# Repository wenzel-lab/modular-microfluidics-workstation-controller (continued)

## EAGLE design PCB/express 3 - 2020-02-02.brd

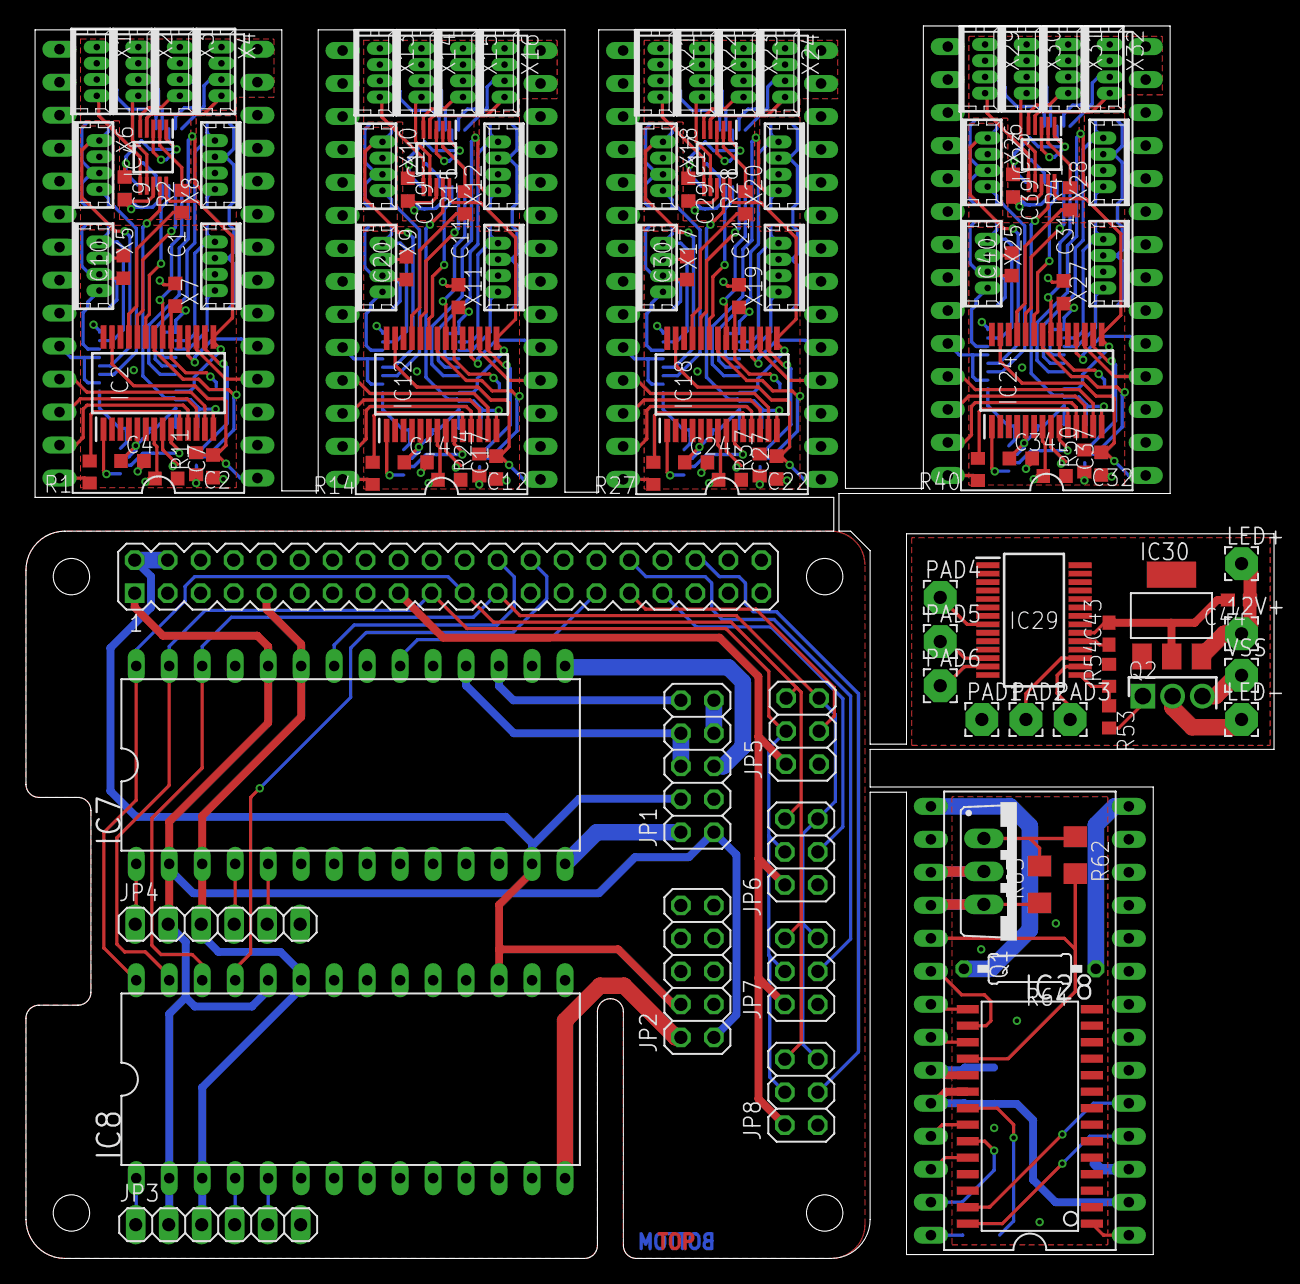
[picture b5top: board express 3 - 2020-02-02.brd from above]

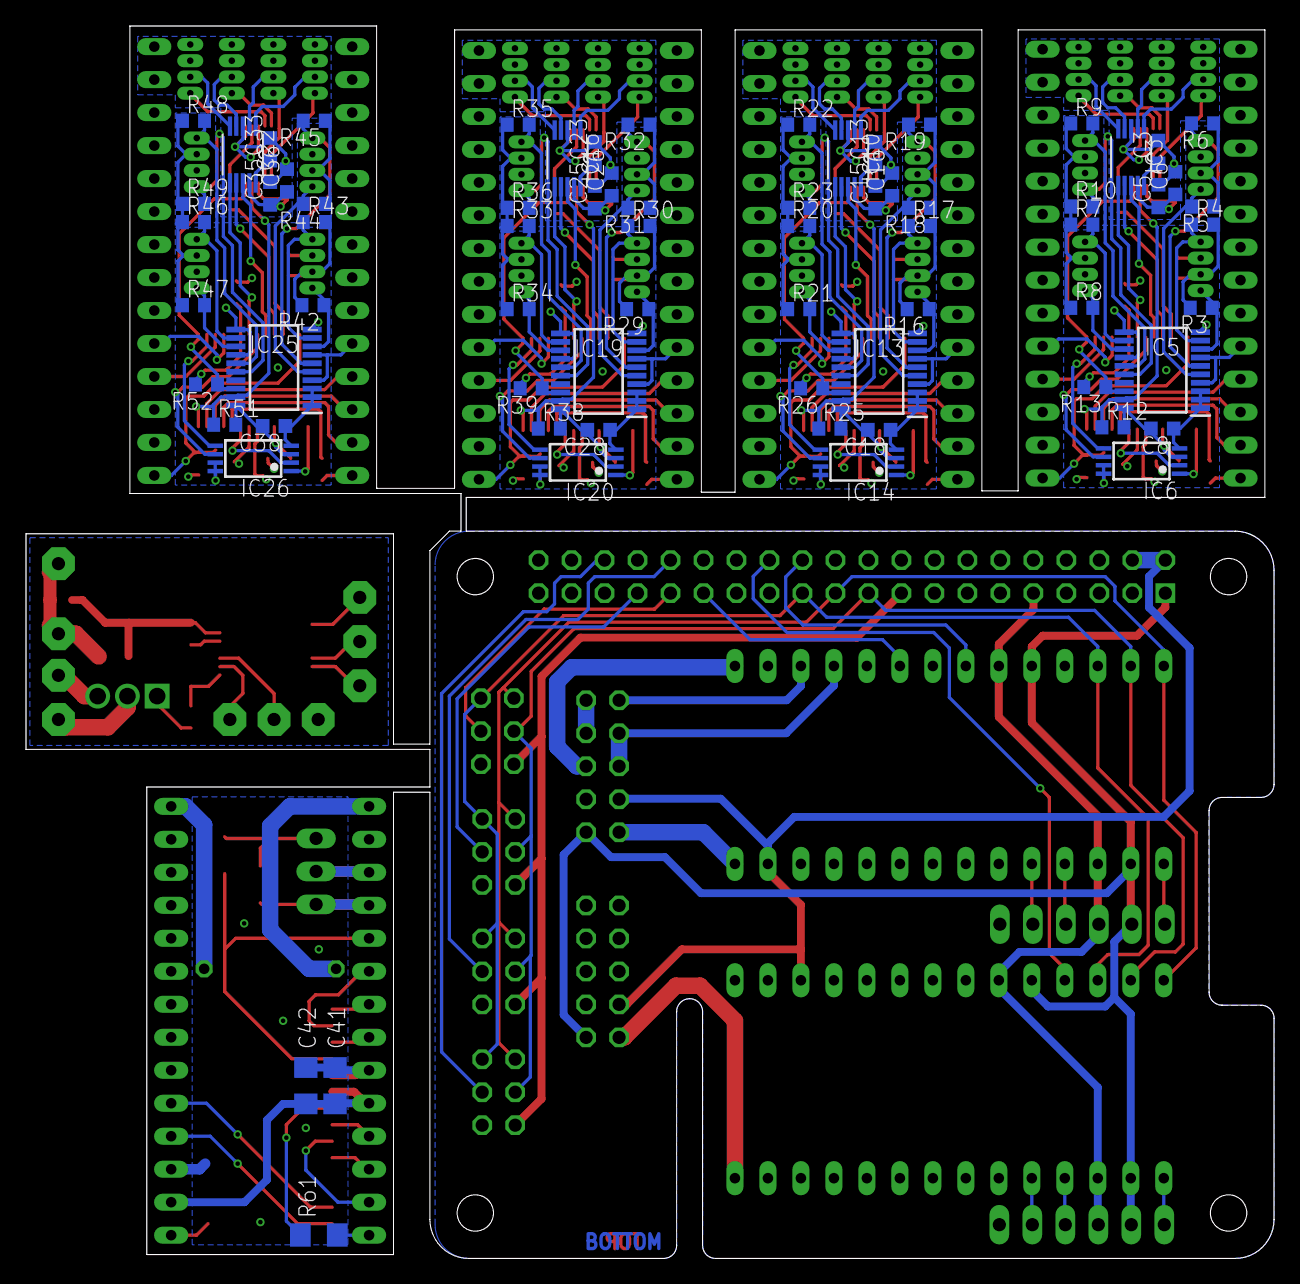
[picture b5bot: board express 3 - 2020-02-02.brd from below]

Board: 4 copper layers, 96.1 x 94.9 mm, 185 parts (71 on the bottom side), 213 nets.

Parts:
12V+: WIREPAD2,54/1,0; 2,54/1,0
C1, C2, C3, C4, C5, C6, C7, C8, C9, C10, C11, C12, C13, C14, C15, C16, C17, C18, C19, C20, C21, C22, C23, C24, C25, C26, C27, C28, C29, C30, C31, C32, C33, C34, C35, C36, C37, C38, C39, C40: C0603K
C41, C42: C1206
C43, C44: C0603
IC1, IC7, IC8, IC9, IC15, IC21, IC27: DIL28-6
IC2, IC12, IC18, IC24: DSPIC33CK256MP502-I_SS; SOP65P780X200-28N
IC3, IC10, IC16, IC22: AD5624R; SOP50P490X110-10N
IC4, IC11, IC17, IC23: ADS1115; SOP50P490X110-10N
IC5, IC13, IC19, IC25: PCA9544APW,112; SOP65P640X110-20N
IC6, IC14, IC20, IC26: 25AA040ST; TSSOP8
IC28: PIC16F18857; SO28W
IC29: PIC16F18857T-I_SS; SOP65P780X200-28N
IC30: REG1117; SOT223
JP1, JP2: 2X05
JP3, JP4: 1X06
JP5, JP6, JP7, JP8: 2X03
K1: PIN20X2; PIN_20X2
LED+: WIREPAD2,54/1,0; 2,54/1,0
LED-: WIREPAD2,54/1,0; 2,54/1,0
PAD1, PAD2, PAD3, PAD4, PAD5, PAD6: WIREPAD2,54/1,0; 2,54/1,0
Q1: TO220BV
Q2: AUIRFU8403; TO229P239X654X978-3P
R1, R2, R3, R4, R5, R6, R7, R8, R9, R10, R11, R12, R13, R14, R15, R16, R17, R18, R19, R20, R21, R22, R23, R24, R25, R26, R27, R28, R29, R30, R31, R32, R33, R34, R35, R36, R37, R38, R39, R40, R41, R42, R43, R44, R45, R46, R47, R48, R49, R50, R51, R52, R53, R54: R0603
R61, R62, R63: R1206
R64: 0207/10
VSS: WIREPAD2,54/1,0; 2,54/1,0
X1, X2, X3, X4, X5, X6, X7, X8, X9, X10, X11, X12, X13, X14, X15, X16, X17, X18, X19, X20, X21, X22, X23, X24, X25, X26, X27, X28, X29, X30, X31, X32: 53047-04

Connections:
0V: IC7.18, JP1.6, JP1.8
+3V1: IC7.2, IC7.24, IC8.2, IC8.24, JP1.1, JP2.1, JP3.2, JP4.2, JP5.2, JP6.2, JP7.2, JP8.2, K1.1, K1.17
+3V2: C11.1, C12.1, C14.1, C18.2, C20.1, IC9.2, IC9.24, IC12.5, IC12.7, IC12.20, IC13.4, IC13.7, IC13.11, IC13.14, IC13.20, IC14.3, IC14.7, IC14.8, R16.2, R17.2, R18.1, R19.1, R20.1, R21.1, R22.1, R23.1, R24.1, R25.2, R26.2, X9.2, X10.2, X11.2, X12.2
+3V3: C1.1, C2.1, C4.1, C8.2, C10.1, IC1.2, IC1.24, IC2.5, IC2.7, IC2.20, IC5.4, IC5.7, IC5.11, IC5.14, IC5.20, IC6.3, IC6.7, IC6.8, R3.2, R4.2, R5.1, R6.1, R7.1, R8.1, R9.1, R10.1, R11.1, R12.2, R13.2, X5.2, X6.2, X7.2, X8.2
+3V4: C21.1, C22.1, C24.1, C28.2, C30.1, IC15.2, IC15.24, IC18.5, IC18.7, IC18.20, IC19.4, IC19.7, IC19.11, IC19.14, IC19.20, IC20.3, IC20.7, IC20.8, R29.2, R30.2, R31.1, R32.1, R33.1, R34.1, R35.1, R36.1, R37.1, R38.2, R39.2, X17.2, X18.2, X19.2, X20.2
+3V5: C31.1, C32.1, C34.1, C38.2, C40.1, IC21.2, IC21.24, IC24.5, IC24.7, IC24.20, IC25.4, IC25.7, IC25.11, IC25.14, IC25.20, IC26.3, IC26.7, IC26.8, R42.2, R43.2, R44.1, R45.1, R46.1, R47.1, R48.1, R49.1, R50.1, R51.2, R52.2, X25.2, X26.2, X27.2, X28.2
+5V: C5.1, C6.1, C9.2, IC1.17, IC3.9, IC4.8
+5V1: IC7.13, IC8.17, JP1.4, JP2.4, K1.2, K1.4
+5V2: C15.1, C16.1, C19.2, IC9.17, IC10.9, IC11.8
+5V3: C25.1, C26.1, C29.2, IC15.17, IC16.9, IC17.8
+5V4: C35.1, C36.1, C39.2, IC21.17, IC22.9, IC23.8
+5V6: C43.2, C44.2, IC29.20, IC30.2
+12V: IC1.14, X1.4, X2.4, X3.4, X4.4
+12V1: IC7.14, IC8.14, JP1.2, JP2.2
+12V2: IC9.14, X13.4, X14.4, X15.4, X16.4
+12V3: IC15.14, X21.4, X22.4, X23.4, X24.4
+12V4: IC21.14, X29.4, X30.4, X31.4, X32.4
+12V5: IC27.14, R64.1
+12V6: 12V+.1, C44.1, IC30.3, LED+.1
ADC_RDY: IC2.25, R2.1
ADC_RDY1: IC12.25, R15.1
ADC_RDY2: IC18.25, R28.1
ADC_RDY3: IC24.25, R41.1
CE0: IC7.22, K1.24
CE1: IC8.25, K1.26
GND: C1.2, C2.2, C3.2, C4.2, C5.2, C6.2, C7.1, C8.1, C9.1, C10.2, IC1.3, IC1.13, IC1.23, IC2.6, IC2.8, IC2.19, IC3.3, IC4.1, IC4.3, IC5.1, IC5.2, IC5.3, IC5.10, IC6.4, X1.3, X2.3, X3.3, X4.3, X5.3, X6.3, X7.3, X8.3
GND1: IC7.3, IC7.23, IC8.3, IC8.13, IC8.23, JP1.3, JP2.3, JP3.3, JP4.3, JP5.1, JP6.1, JP7.1, JP8.1, K1.6, K1.9, K1.14, K1.20, K1.25, K1.30, K1.34, K1.39
GND2: C11.2, C12.2, C13.2, C14.2, C15.2, C16.2, C17.1, C18.1, C19.1, C20.2, IC9.3, IC9.13, IC9.23, IC10.3, IC11.1, IC11.3, IC12.6, IC12.8, IC12.19, IC13.1, IC13.2, IC13.3, IC13.10, IC14.4, X9.3, X10.3, X11.3, X12.3, X13.3, X14.3, X15.3, X16.3
GND3: C21.2, C22.2, C23.2, C24.2, C25.2, C26.2, C27.1, C28.1, C29.1, C30.2, IC15.3, IC15.13, IC15.23, IC16.3, IC17.1, IC17.3, IC18.6, IC18.8, IC18.19, IC19.1, IC19.2, IC19.3, IC19.10, IC20.4, X17.3, X18.3, X19.3, X20.3, X21.3, X22.3, X23.3, X24.3
GND4: C31.2, C32.2, C33.2, C34.2, C35.2, C36.2, C37.1, C38.1, C39.1, C40.2, IC21.3, IC21.13, IC21.23, IC22.3, IC23.1, IC23.3, IC24.6, IC24.8, IC24.19, IC25.1, IC25.2, IC25.3, IC25.10, IC26.4, X25.3, X26.3, X27.3, X28.3, X29.3, X30.3, X31.3, X32.3
GND5: C41.2, C42.2, IC27.3, IC27.23, IC28.8, IC28.19
GPIO6: JP5.3, K1.31
GPIO12: JP7.3, K1.32
GPIO13: JP6.3, K1.33
GPIO16: JP8.3, K1.36
I2C_SCL: IC2.15, IC4.10, IC5.18, R13.1
I2C_SCL1: IC11.10, IC12.15, IC13.18, R26.1
I2C_SCL2: IC17.10, IC18.15, IC19.18, R39.1
I2C_SCL3: IC23.10, IC24.15, IC25.18, R52.1
I2C_SDA: IC2.14, IC4.9, IC5.19, R12.1
I2C_SDA1: IC11.9, IC12.14, IC13.19, R25.1
I2C_SDA2: IC17.9, IC18.14, IC19.19, R38.1
I2C_SDA3: IC23.9, IC24.14, IC25.19, R51.1
ICSP_MCLR: C7.2, IC1.1, IC2.27, R11.2
ICSP_MCLR1: IC8.1, JP3.1
ICSP_MCLR2: IC7.1, JP4.1
ICSP_MCLR3: C17.2, IC9.1, IC12.27, R24.2
ICSP_MCLR4: C27.2, IC15.1, IC18.27, R37.2
ICSP_MCLR5: C37.2, IC21.1, IC24.27, R50.2
ICSP_MCLR6: IC27.1, IC28.1
ICSP_PGC: IC1.5, IC2.18
ICSP_PGC1: IC8.5, JP3.5
ICSP_PGC2: IC7.5, JP4.5
ICSP_PGC3: IC9.5, IC12.18
ICSP_PGC4: IC15.5, IC18.18
ICSP_PGC5: IC21.5, IC24.18
ICSP_PGD: IC1.4, IC2.17
ICSP_PGD1: IC8.4, JP3.4
ICSP_PGD2: IC7.4, JP4.4
ICSP_PGD3: IC9.4, IC12.17
ICSP_PGD4: IC15.4, IC18.17
ICSP_PGD5: IC21.4, IC24.17
ICSP_PGD6: IC27.4, IC28.28
LED_-: LED-.1, Q2.2
LED_LOW: IC29.15, R53.1, R54.1
MISO: IC7.28, IC8.28, JP5.6, JP6.6, JP7.6, JP8.6, K1.21
MOSI: IC7.27, IC8.27, JP5.4, JP6.4, JP7.4, JP8.4, K1.19
unnamed: C3.1, IC3.10
unnamed: IC3.1, X1.2
unnamed: IC11.2, R15.2
unnamed: IC11.5, X15.1
unnamed: C13.1, IC10.10
unnamed: IC3.2, X2.2
unnamed: IC3.4, X3.2
unnamed: IC4.2, R2.2
unnamed: IC10.1, X13.2
unnamed: IC4.5, X3.1
unnamed: IC3.5, X4.2
unnamed: IC5.5, R5.2, X6.1
unnamed: IC5.6, R6.2, X6.4
unnamed: IC5.8, R3.1, X5.1
unnamed: IC5.9, R4.1, X5.4
unnamed: IC5.12, R7.2, X7.1
unnamed: IC5.13, R8.2, X7.4
unnamed: IC5.15, R9.2, X8.1
unnamed: IC5.16, R10.2, X8.4
unnamed: IC4.7, X2.1
unnamed: IC10.2, X14.2
unnamed: IC4.6, X1.1
unnamed: IC4.4, X4.1
unnamed: IC10.4, X15.2
unnamed: IC10.5, X16.2
unnamed: IC13.12, R20.2, X11.1
unnamed: IC13.13, R21.2, X11.4
unnamed: IC13.15, R22.2, X12.1
unnamed: IC13.16, R23.2, X12.4
unnamed: IC13.5, R18.2, X10.1
unnamed: IC13.6, R19.2, X10.4
unnamed: IC13.8, R16.1, X9.1
unnamed: IC13.9, R17.1, X9.4
unnamed: IC11.7, X14.1
unnamed: IC11.6, X13.1
unnamed: IC11.4, X16.1
unnamed: IC17.2, R28.2
unnamed: IC17.5, X23.1
unnamed: C23.1, IC16.10
unnamed: IC16.1, X21.2
unnamed: IC16.2, X22.2
unnamed: IC16.4, X23.2
unnamed: IC16.5, X24.2
unnamed: IC19.12, R33.2, X19.1
unnamed: IC19.13, R34.2, X19.4
unnamed: IC19.15, R35.2, X20.1
unnamed: IC19.16, R36.2, X20.4
unnamed: IC19.5, R31.2, X18.1
unnamed: IC19.6, R32.2, X18.4
unnamed: IC19.8, R29.1, X17.1
unnamed: IC19.9, R30.1, X17.4
unnamed: IC17.7, X22.1
unnamed: IC17.6, X21.1
unnamed: IC17.4, X24.1
unnamed: IC23.2, R41.2
unnamed: IC23.5, X31.1
unnamed: C33.1, IC22.10
unnamed: IC22.1, X29.2
unnamed: IC22.2, X30.2
unnamed: IC22.4, X31.2
unnamed: IC22.5, X32.2
unnamed: IC25.12, R46.2, X27.1
unnamed: IC25.13, R47.2, X27.4
unnamed: IC25.15, R48.2, X28.1
unnamed: IC25.16, R49.2, X28.4
unnamed: IC25.5, R44.2, X26.1
unnamed: IC25.6, R45.2, X26.4
unnamed: IC25.8, R42.1, X25.1
unnamed: IC25.9, R43.1, X25.4
unnamed: IC23.7, X30.1
unnamed: IC23.6, X29.1
unnamed: IC23.4, X32.1
unnamed: IC27.25, IC28.22
unnamed: IC28.21, R61.2
unnamed: IC27.5, IC28.27
unnamed: Q1.G, R62.1, R63.2
unnamed: IC27.21, IC28.15
unnamed: Q2.1, R53.2
SCLK: IC7.26, IC8.26, JP5.5, JP6.5, JP7.5, JP8.5, K1.23
SPI2_DAC_CLK: IC2.24, IC3.7
SPI2_DAC_CLK1: IC10.7, IC12.24
SPI2_DAC_CLK2: IC16.7, IC18.24
SPI2_DAC_CLK3: IC22.7, IC24.24
SPI2_DAC_MOSI: IC2.23, IC3.8
SPI2_DAC_MOSI1: IC10.8, IC12.23
SPI2_DAC_MOSI2: IC16.8, IC18.23
SPI2_DAC_MOSI3: IC22.8, IC24.23
SPI2_DAC_SYNC: IC2.21, IC3.6
SPI2_DAC_SYNC1: IC10.6, IC12.21
SPI2_DAC_SYNC2: IC16.6, IC18.21
SPI2_DAC_SYNC3: IC22.6, IC24.21
SPI3_EE_CLK: IC2.22, IC6.6
SPI3_EE_CLK1: IC12.22, IC14.6
SPI3_EE_CLK2: IC18.22, IC20.6
SPI3_EE_CLK3: IC24.22, IC26.6
SPI3_EE_MISO: IC2.9, IC6.2
SPI3_EE_MISO1: IC12.9, IC14.2
SPI3_EE_MISO2: IC18.9, IC20.2
SPI3_EE_MISO3: IC24.9, IC26.2
SPI3_EE_MOSI: IC2.16, IC6.5
SPI3_EE_MOSI1: IC12.16, IC14.5
SPI3_EE_MOSI2: IC18.16, IC20.5
SPI3_EE_MOSI3: IC24.16, IC26.5
SPI3_EE_SS: IC2.1, IC6.1
SPI3_EE_SS1: IC12.1, IC14.1
SPI3_EE_SS2: IC18.1, IC20.1
SPI3_EE_SS3: IC24.1, IC26.1
SPI_CLK: IC1.26, IC2.12
SPI_CLK1: IC9.26, IC12.12
SPI_CLK2: IC15.26, IC18.12
SPI_CLK3: IC21.26, IC24.12
SPI_CLK4: IC27.26, IC28.24
SPI_IN: IC1.27, IC2.11
SPI_IN1: IC9.27, IC12.11
SPI_IN2: IC15.27, IC18.11
SPI_IN3: IC21.27, IC24.11
SPI_IN4: IC27.27, IC28.23
SPI_OUT: IC1.28, R1.2
SPI_OUT1: IC9.28, R14.2
SPI_OUT2: IC15.28, R27.2
SPI_OUT3: IC21.28, R40.2
SPI_OUT4: IC27.28, R61.1
SPI_OUT_R: IC2.10, R1.1
SPI_OUT_R1: IC12.10, R14.1
SPI_OUT_R2: IC18.10, R27.1
SPI_OUT_R3: IC24.10, R40.1
SPI_SS: IC1.25, IC2.13
SPI_SS1: IC9.25, IC12.13
SPI_SS2: IC15.25, IC18.13
SPI_SS3: IC21.25, IC24.13
SPI_SS4: IC27.22, IC28.17
STROBE+: JP1.7, JP1.9
STROBE+_RES: IC7.15, JP1.5
STROBE+_RES1: IC27.15, R64.2
STROBE-: IC7.17, JP1.10
STROBE-1: IC27.17, Q1.D
STROBE_0V: IC27.18, Q1.S, R63.1
STROBE_GATE1: IC27.19, IC28.18, R62.2
STROBE_TRIG_IN: IC7.20, K1.29
STROBE_TRIG_IN1: IC27.20, IC28.16
SW1.1: IC29.17, PAD2.1
SW1.2: IC29.16, PAD3.1
SW2.1: IC29.12, PAD5.1
SW2.2: IC29.13, PAD6.1
V+: C41.1, C42.1, IC27.2, IC27.24, IC28.20
VSS: C43.1, IC29.8, IC29.19, IC30.1, PAD1.1, PAD4.1, Q2.3, R54.2, VSS.1

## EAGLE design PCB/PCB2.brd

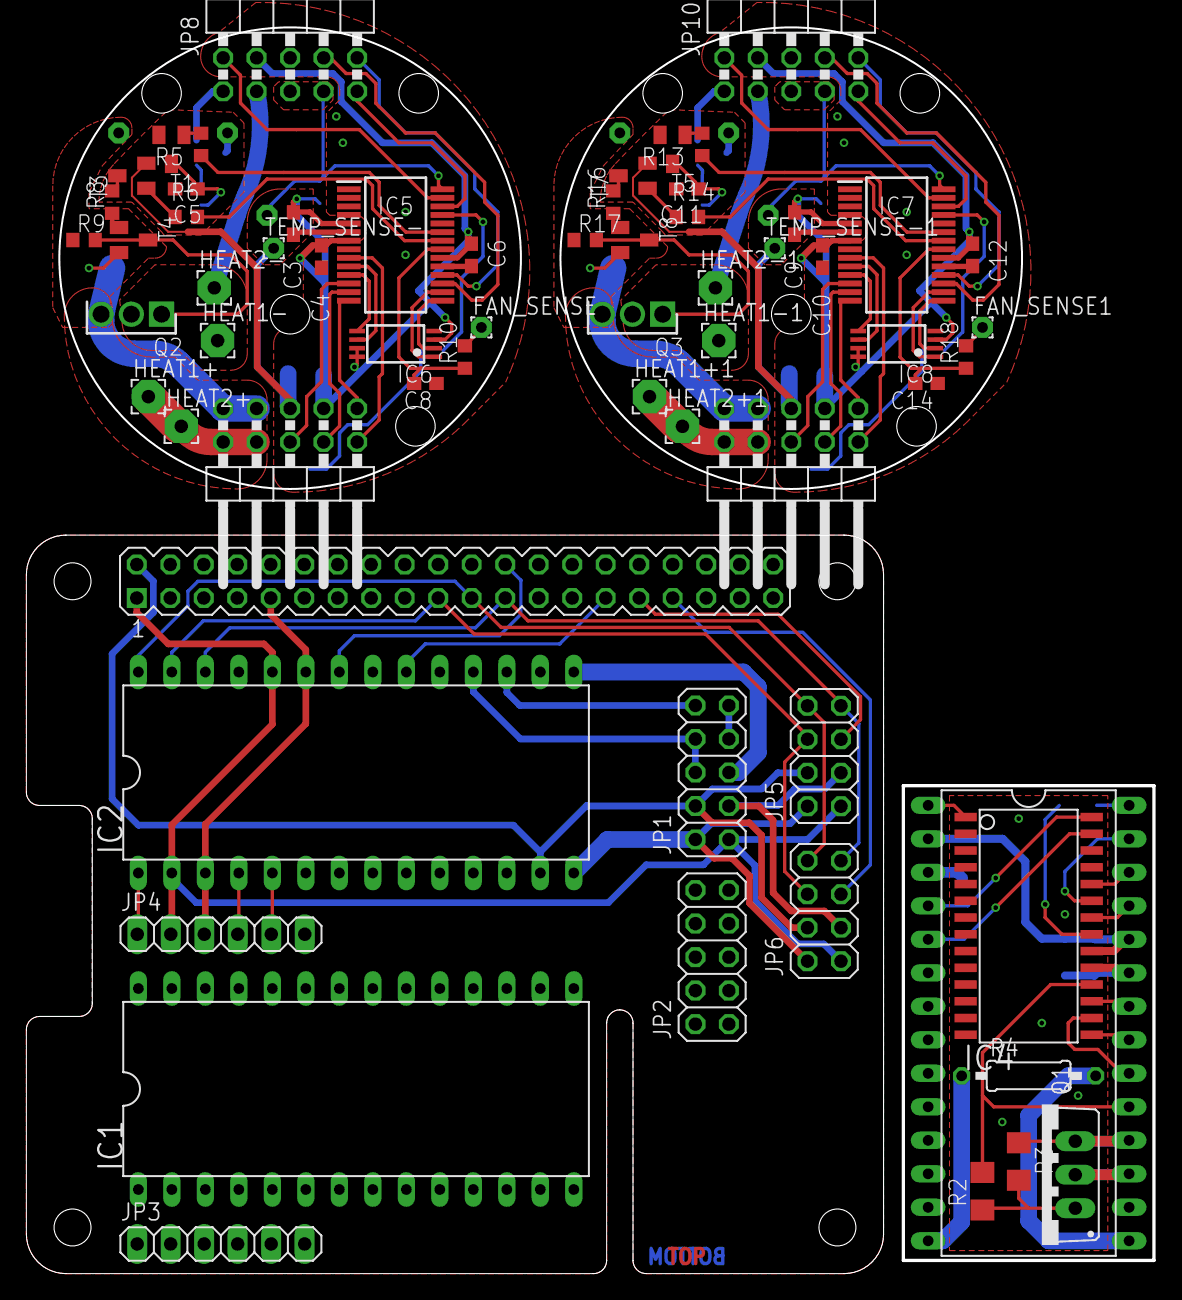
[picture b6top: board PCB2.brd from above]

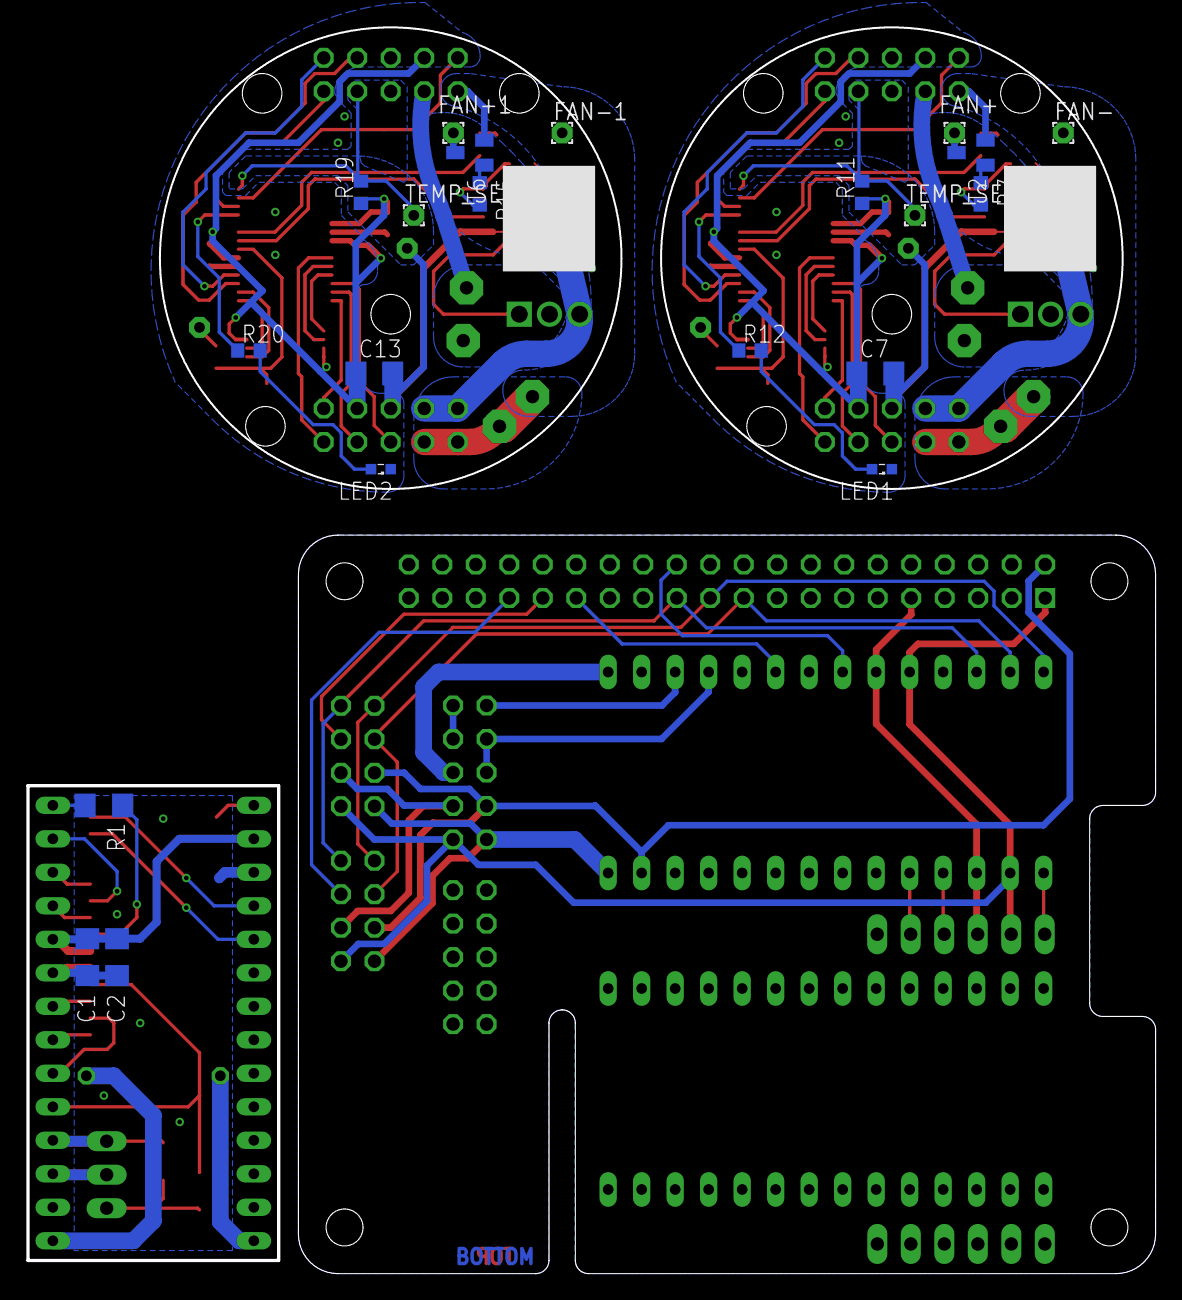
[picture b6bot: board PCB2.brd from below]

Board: 2 copper layers, 85.5 x 94.5 mm, 84 parts (21 on the bottom side), 101 nets.

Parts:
C1, C2, C7, C13: C1206
C3, C4, C5, C6, C8, C9, C10, C11, C12, C14: C0603
FAN+, FAN+1: 1,6/0,8
FAN-, FAN-1: 1,6/0,8
FAN_SENSE, FAN_SENSE1: 1,6/0,8
HEAT1+, HEAT1+1, HEAT1-, HEAT1-1, HEAT2+, HEAT2+1, HEAT2-, HEAT2-1: 2,54/1,0
IC1, IC2, IC3: DIL28-6
IC4: PIC16F18857; SO28W
IC5, IC7: DSPIC33CK256MP502-I_SS; SOP65P780X200-28N
IC6, IC8: 25AA040ST; TSSOP8
JP1, JP2: 2X05
JP3, JP4: 1X06
JP5, JP6: 2X04
JP7, JP8, JP9, JP10: 2X05/90
K1: PIN20X2; PIN_20X2
LED1, LED2: SML0603
Q1: TO220BV
Q2, Q3: AUIRFU8403; TO229P239X654X978-3P
R1, R2, R3: R1206
R4: 0207/10
R5, R6, R7, R8, R9, R10, R11, R12, R13, R14, R15, R16, R17, R18, R19, R20: R0603
T1, T2, T3, T4, T5, T6, T7, T8: SOT23-BEC
TEMP_SENSE+, TEMP_SENSE+1: 1,6/0,8
TEMP_SENSE-, TEMP_SENSE-1: 1,6/0,8

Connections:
0V: IC2.18, JP1.6, JP1.8
0V1: FAN-.1, JP7.7, JP7.9, Q2.3, R9.1
0V2: FAN-1.1, JP9.7, JP9.9, Q3.3, R17.1
+3V1: C3.1, C4.1, C6.1, C7.1, IC5.5, IC5.7, IC5.20, IC6.3, IC6.7, IC6.8, JP7.3, JP8.4, R11.1
+3V2: C9.1, C10.1, C12.1, C13.1, IC7.5, IC7.7, IC7.20, IC8.3, IC8.7, IC8.8, JP9.3, JP10.4, R19.1
+3V3: IC2.2, IC2.24, JP1.1, JP4.2, JP5.1, JP6.1, K1.1, K1.17
+5V: IC2.13, JP1.4, JP5.4, JP6.4, K1.2, K1.4
+12V: IC2.14, JP1.2, JP5.2, JP6.2
+12V1: IC3.14, R4.1
+12V2: HEAT1+.1, HEAT2+.1, JP7.8, JP7.10, JP8.1, T2.E, T4.E
+12V3: HEAT1+1.1, HEAT2+1.1, JP9.8, JP9.10, JP10.1, T6.E, T8.E
CE0: IC2.22, K1.24
FAN+: FAN+.1, T2.C
FAN+1: FAN+1.1, T6.C
FAN_SENSE: C8.2, IC5.21, R10.1
FAN_SENSE1: C14.2, IC7.21, R18.1
GND: IC2.3, IC2.23, JP1.3, JP4.3, JP5.3, JP6.3, K1.6, K1.9, K1.14, K1.20, K1.25, K1.30, K1.34, K1.39
GND1: C1.2, C2.2, IC3.3, IC3.23, IC4.8, IC4.19
GND2: C3.2, C4.2, C5.2, C6.2, C7.2, C8.1, IC5.6, IC5.8, IC5.19, IC6.4, JP7.5, JP8.5, JP8.6, LED1.C, T1.E, T3.E, TEMP_SENSE-.1
GND3: C9.2, C10.2, C11.2, C12.2, C13.2, C14.1, IC7.6, IC7.8, IC7.19, IC8.4, JP9.5, JP10.5, JP10.6, LED2.C, T5.E, T7.E, TEMP_SENSE-1.1
GPIO6: JP5.5, K1.31
GPIO13: JP6.5, K1.33
HEAT-: HEAT1-.1, HEAT2-.1, JP8.3, Q2.2
HEAT-1: HEAT1-1.1, HEAT2-1.1, JP10.3, Q3.2
ICSP_MCLR: IC2.1, JP4.1
ICSP_PGC: IC2.5, JP4.5
ICSP_PGD: IC2.4, JP4.4
ISCP_PGD: IC3.4, IC4.28
MCLR: IC5.27, JP8.2
MCLR1: IC7.27, JP10.2
MISO: IC2.28, JP5.8, JP6.8, K1.21
MOSI: IC2.27, JP5.6, JP6.6, K1.19
unnamed: IC3.25, IC4.22
unnamed: IC4.21, R1.2
unnamed: R8.2, T3.C
unnamed: R8.1, T4.B
unnamed: IC3.5, IC4.27
unnamed: R5.1, T1.B
unnamed: C5.1, R7.2, T1.C
unnamed: R7.1, T2.B
unnamed: Q1.G, R2.1, R3.2
unnamed: R6.1, T3.B
unnamed: IC3.21, IC4.15
unnamed: Q2.1, R9.2, T4.C
unnamed: FAN_SENSE.1, R10.2
unnamed: IC5.11, IC6.5
unnamed: IC5.10, IC6.6
unnamed: IC5.15, IC6.2
unnamed: IC5.16, IC6.1
unnamed: IC5.22, R6.2
unnamed: IC5.23, R5.2
unnamed: LED1.A, R12.2
unnamed: IC5.25, R12.1
unnamed: R13.1, T5.B
unnamed: R15.1, T6.B
unnamed: C11.1, R15.2, T5.C
unnamed: R16.2, T7.C
unnamed: R16.1, T8.B
unnamed: R14.1, T7.B
unnamed: Q3.1, R17.2, T8.C
unnamed: FAN_SENSE1.1, R18.2
unnamed: IC7.11, IC8.5
unnamed: IC7.10, IC8.6
unnamed: IC7.15, IC8.2
unnamed: IC7.16, IC8.1
unnamed: IC7.22, R14.2
unnamed: IC7.23, R13.2
unnamed: LED2.A, R20.2
unnamed: IC7.25, R20.1
PGC: IC5.18, JP8.10
PGC1: IC7.18, JP10.10
PGD: IC5.17, JP8.8
PGD1: IC7.17, JP10.8
SCLK: IC2.26, JP5.7, JP6.7, K1.23
SPI1: IC5.9, JP7.2
SPI2: IC5.12, JP7.6
SPI3: IC5.13, JP7.4
SPI4: IC5.14, JP7.1
SPI5: IC7.9, JP9.2
SPI6: IC7.12, JP9.6
SPI7: IC7.13, JP9.4
SPI8: IC7.14, JP9.1
SPI_CLOCK: IC3.26, IC4.24
SPI_IN: IC3.27, IC4.23
SPI_MCLR: IC3.1, IC4.1
SPI_OUT: IC3.28, R1.1
SPI_SS: IC3.22, IC4.17
STROBE+: JP1.7, JP1.9
STROBE+_RES: IC2.15, JP1.5
STROBE+_RES1: IC3.15, R4.2
STROBE-: IC2.17, JP1.10
STROBE-1: IC3.17, Q1.D
STROBE_0V: IC3.18, Q1.S, R3.1
STROBE_GATE1: IC3.19, IC4.18, R2.2
STROBE_TRIG_IN: IC2.20, K1.29
STROBE_TRIG_IN1: IC3.20, IC4.16
TEMP_SENSE: IC5.28, JP8.7, R11.2, TEMP_SENSE+.1
TEMP_SENSE1: IC7.28, JP10.7, R19.2, TEMP_SENSE+1.1
TX: IC5.26, JP8.9
TX1: IC7.26, JP10.9
V+: C1.1, C2.1, IC3.2, IC3.24, IC4.20

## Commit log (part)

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2019-08-20 Create blank
2019-10-01 nbproject folder added.
2019-10-01 All files added. Can output 2ms pulse after camera start pulse.
2019-10-03 Can set strobe timing via time parameters.
2019-10-04 Adding CLC code.
2019-10-04 SPI strobe interface working.
2019-10-05 STX added.
2019-10-05 Checksum and corruption test.
2019-10-05 Created basic packet routines.
2019-10-07 Fixed MAX_TIME_NS and strobe timing packet parse.
2019-10-08 Strobe MAX_TIME_NS fixed.
2019-10-08 Fixed abs calculation in find_scalers_time. Changed TMR2 to trigger on transition instead of level - this allows strobe optionally to be on during closing shutter. Had to leave TMR4 on to make this w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
2019-10-08 Added strobe camera class. Attempts to calculate camera timing.
2019-10-08 New time calculations.
2019-10-11 Testing GUI development.
2019-10-12 Strobe PIC return comms.
2019-10-14 Auto adjust camera timing using camera read back time capture.
2019-10-19 Initial PCB for strobe module.
2019-10-19 Raspberry Pi 4 config to output camera "strobe" on GPIO.
2019-10-26 Initial commit. DAC write works.
2019-10-28 Continuous ADC conversion success.
2019-10-28 SPI test code compiles.
2019-10-29 SPI receive packets.
2019-10-30 SPI transmit modified not to write TX when not data to write (unlike with PIC16 series). Tests good.
2019-11-09 Started ADC <-> mbar conversion code. Starting ADS1115 implementation.
2019-11-10 ADS1115 working (polling).
2019-11-12 Fixed PIC clock. Added 1ms timer. I2C fixed - SEN was set while PEN - prevent manual ISR if PEN.
2019-11-14 Combined and improved ADS1115 I2C.
2019-11-15 ADC I2C polled for completion instead of waiting.
2019-11-19 Heater PID and simulated heater.
2019-11-20 Good temperature readings via UART. Heater heating manual power.
2019-12-05 Developing protocols and autotune status.
2019-12-05 Protocol working (ID and get temp). Changed IRQ priority such that SPI can't be interrupted.
2019-12-25 EEPROM and storage libraries created. Fan/stirrer output, speed measurement and control implemented.
2020-01-05 First strobe PCB submitted.
2020-01-05 Stirrer fan PID implemented. ADC trigger changed to timer. Measures 2.5us per sample x 16 = 40us filter interrupt.
2020-01-05 Submitting old PCB design before replacing with new design.
2020-01-05 First combined PCB for manufacture - pi hat, strobe, sample holder.
2020-01-16 Added resistor.
2020-01-16 Some config change?
2020-01-16 Stir interface + EEPROM added. LED added. Pins moved to match PCB. Fixed intermittent 10-bit readings - caused by reading filter register in main loop resetting RDY flag. 16-bit temperature readings.
2020-01-16 Minor changes to PCB: 1mm larger, MCLR resistor + cap added, thicker trace to external heater. Second manufacturing, not express.
2020-01-19 Added bulk cap and changed caps to Kemet, which have smaller keepout.
2020-01-19 Express manufacture - 4 layer pressure/flow board, pi hat, strobe.
2020-01-20 PCB modifications to get I2C on correct pins and use extra SPI for EEPROM. Code updated to match new pinout.
2020-01-21 ADC functional. Also fixed ADC RDY thresholds, which are 16-bit, not 8-bit.
2020-01-22 EEPROM working. DAC internal reference working.
2020-01-22 Storage added.
2020-01-26 Updated to match PCB. Programmed successfully, plugged into Pi Hat on Pi.
2020-01-28 Strobe PCB SPI working.
2020-01-28 Added PCA9544A I2C MUX and tested via Sensirion.
2020-01-29 Sensirion read flow/temp/flags implemented.
2020-01-30 Continuous pressure readings and pressure output, correctly scaled.
2020-02-01 More allowance between ICs and caps.
2020-02-02 Express PCB 3 ready.
2020-02-11 Caps moved to allow larger gaps near ADC, DAC, connector.
2020-02-11 Module headers replaced.
2020-02-11 Production commit.
2020-02-12 External strobe trigger added. Text and boxes added.
2020-02-16 Working on picommon.py, which controls SPI across all devices.
2020-02-16 Start of GUI.
2020-02-17 Added power limit setting. Expanded error capabilities.
2020-02-17 Heater display created as class. Fixed various general errors.
2020-02-23 New strobe interface code and GUI.
2020-02-23 Using piholderbox.py.
2020-02-23 Using pistrobebox.py.
2020-02-23 EEPROM storage save is now readwrite.
2020-02-23 Fan tuning. Save temps in EEPROM when set. Option to autotune for no overshoot. Saves power limit. Optional code to write current limit on start.
2020-02-24 Removed pull-ups on SDI and CLK. Problem caused by soldering and pull-ups were probably fine.
2020-02-25 Shipping.
2020-03-01 Changed fan sense resistor from 1k to 510, because at low speed the fan feedback would not pull low enough.
2020-03-01 Added SPI names.
2020-03-01 Added stir functions.
2020-03-06 Sample holder PCB images.
2020-03-06 Component placement images.
2020-03-07 Sample Holder image.
2020-03-10 EEPROM SS moved to RA1, tests OK. Snap programmer. Starting LG16 interface.
2020-03-10 Sensirion LG16 library working. Still need to integrate new functions.
2020-03-11 Restored lost changes. LG16 sensor now active, startup init added. Channel mapping added.
2020-03-13 Component values added.
2020-03-17 add more files for sample reservoirs
2020-03-19 image of 100ml reservoir added
2020-03-19 add bottle reservoir image
2020-03-19 remove unneeded old text
2020-03-23 Sample holder 3D images.
2020-03-25 ADC error handling. Pressure and flow control modes. Added control commands. LG16 flow sensor support.
2020-05-04 Creating Flask webapp.
2020-05-04 Automatic updates test.
2020-05-05 Continuous threaded updates working.
2020-05-08 Web interface for heater/piholder.
2020-05-09 Workaround for time.sleep in piholder.py and strobe.py. time.sleep would not return if the other thread blocked to obtain lock.
2020-05-09 Corrected initial copying of jinja strobe data. Added strobe period field using input box.
2020-05-10 Heater temperature set.
2020-05-11 Heater web interface complete.
2020-05-22 Mako camera test working.
2020-05-24 Camera html moved to separate file. Camera snapshot working. Camera thread is terminated on exit.
2020-05-29 Improvement of cap holder design
    Added fillets, so that the inner hexagon corners of the cap holder can be machined. 2mm rounded fillet used.
2020-06-27 Flow PIC SPI code copied from heater module. Initial webserver flow implementation.
2020-06-29 Set and get target pressures via webserver.
2020-06-30 Set and get flow control mode.
2020-07-03 MCC file change?
2020-07-03 Update readme.md
    Corrected MOSFET name.
2020-07-03 Flow rate read and displayed.
2020-07-06 Negligible changes.
2020-07-15 PICkit3 profiles.
2020-07-15 Get and set sample holder power limit.
2020-07-21 Sample holder init retries.
2020-07-27 Flow PID, controlling rate of change. Works very well.
2020-07-27 Webserver set target flow rate.
2020-07-28 Get/set flow control PID constants. Works great.
2020-07-30 Webserver can run without camera (untested) and camera can be switched. Broken pipe error caused by video stream when switching to None, which causes delay.
2020-08-13 added LED holder design
2020-08-20 Changed snapshots folder to /home/pi/snapshots.
2020-11-09 Changed png to jpg.
2020-11-11 PCB documentation and images.
2020-11-11 PCB documentation.
2020-11-11 PIC configurations.
2022-12-16 solved typo
2023-02-05 update readme with FADS (sorting) repository
2023-02-05 update with high pressure link
2023-02-06 Web App Zip File
2023-02-06 Web App requirements
2023-02-06 Bump werkzeug from 0.14.1 to 0.15.5 in /module-pi
    Bumps [werkzeug](https://github.com/pallets/werkzeug) from 0.14.1 to 0.15.5.
    - [Release notes](https://github.com/pallets/werkzeug/releases)
    - [Changelog](https://github.com/pallets/werkzeug/blob/main/CHANGES.rst)
    - [Commits](https://github.com/pallets/werkzeug/compare/0.14.1...0.15.5)
    ---
    updated-dependencies:
2023-02-06 Update Software installation link
2023-02-07 add camera information
2023-02-15 Bump werkzeug from 0.14.1 to 2.2.3 in /module-pi
    Bumps [werkzeug](https://github.com/pallets/werkzeug) from 0.14.1 to 2.2.3.
    - [Release notes](https://github.com/pallets/werkzeug/releases)
    - [Changelog](https://github.com/pallets/werkzeug/blob/main/CHANGES.rst)
    - [Commits](https://github.com/pallets/werkzeug/compare/0.14.1...2.2.3)
    ---
    updated-dependencies:
2023-07-23 Update LICENSE - CERN Open Hardware Licence Version 2 - Weakly Reciprocal
2023-07-25 SEMS 2023
2023-10-25 Bump werkzeug from 0.14.1 to 3.0.1 in /module-pi
    Bumps [werkzeug](https://github.com/pallets/werkzeug) from 0.14.1 to 3.0.1.
    - [Release notes](https://github.com/pallets/werkzeug/releases)
    - [Changelog](https://github.com/pallets/werkzeug/blob/main/CHANGES.rst)
    - [Commits](https://github.com/pallets/werkzeug/compare/0.14.1...3.0.1)
    ---
    updated-dependencies:
2023-11-23 Create software folder
2023-11-23 Upload the zip file of the web app
    This version is used at Wenzel Lab
2023-11-23 Move file to software folder
2023-11-23 Bump jinja2 from 2.10 to 2.11.3 in /software
    Bumps [jinja2](https://github.com/pallets/jinja) from 2.10 to 2.11.3.
    - [Release notes](https://github.com/pallets/jinja/releases)
    - [Changelog](https://github.com/pallets/jinja/blob/main/CHANGES.rst)
    - [Commits](https://github.com/pallets/jinja/compare/2.10...2.11.3)
    ---
    updated-dependencies:
2023-11-23 Bump pillow from 9.4.0 to 10.0.1 in /software
    Bumps [pillow](https://github.com/python-pillow/Pillow) from 9.4.0 to 10.0.1.
    - [Release notes](https://github.com/python-pillow/Pillow/releases)
    - [Changelog](https://github.com/python-pillow/Pillow/blob/main/CHANGES.rst)
    - [Commits](https://github.com/python-pillow/Pillow/compare/9.4.0...10.0.1)
    ---
    updated-dependencies:
2023-11-23 Bump flask from 1.0.2 to 2.2.5 in /software
    Bumps [flask](https://github.com/pallets/flask) from 1.0.2 to 2.2.5.
    - [Release notes](https://github.com/pallets/flask/releases)
    - [Changelog](https://github.com/pallets/flask/blob/main/CHANGES.rst)
    - [Commits](https://github.com/pallets/flask/compare/1.0.2...2.2.5)
    ---
    updated-dependencies:
2024-01-23 Bump pillow from 9.4.0 to 10.2.0 in /software
    Bumps [pillow](https://github.com/python-pillow/Pillow) from 9.4.0 to 10.2.0.
    - [Release notes](https://github.com/python-pillow/Pillow/releases)
    - [Changelog](https://github.com/python-pillow/Pillow/blob/main/CHANGES.rst)
    - [Commits](https://github.com/python-pillow/Pillow/compare/9.4.0...10.2.0)
    ---
    updated-dependencies:
2024-03-14 Update readme.md
    add information about the programming interface
2024-04-03 Bump pillow from 9.4.0 to 10.3.0 in /software
    Bumps [pillow](https://github.com/python-pillow/Pillow) from 9.4.0 to 10.3.0.
    - [Release notes](https://github.com/python-pillow/Pillow/releases)
    - [Changelog](https://github.com/python-pillow/Pillow/blob/main/CHANGES.rst)
    - [Commits](https://github.com/python-pillow/Pillow/compare/9.4.0...10.3.0)
    ---
    updated-dependencies:
2024-05-20 Update README.md
    Add a name
2024-09-26 Update readme.md
    Flow cable.
2024-09-26 Update readme.md
    Spacing
2024-09-27 Update PICkit3
2024-09-27 Update directory structure of the project
2024-09-27 Rename software folder
2024-10-03 Update readme.md
    Corrected IC designations.
2024-10-08 Update readme.md
    Added Electro-Pneumatic Cable.
2024-10-08 Update Bill-of-Materials.csv
    Added cables to BOM.
2024-10-14 Create images folder
2025-01-13 Update folder structure
2025-01-14 Update README content
2025-01-15 Update software information
2025-01-15 Fix typo
2025-01-15 Update strobe imaging module
2025-01-17 Update LICENSE section
2025-01-30 Update main README file
2025-01-31 Update BOM of strobe controller
2025-01-31 Update BOM of Pi HAT
2025-06-12 Update of documentation
    New content for the Pi HAT and the Pressure and Flow Controller
2025-06-12 Update user interface software
    New features:
    - Imaging Module: save videos
    - Infusion Module: calibration for fluorinated oil and mineral oil
    - Desktop shortcut for GUI
